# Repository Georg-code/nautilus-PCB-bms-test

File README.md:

# Generation complete!
# NAUTILUS Bms Test Board

# Include documentation here
The documentation can be very similar to your wiki article

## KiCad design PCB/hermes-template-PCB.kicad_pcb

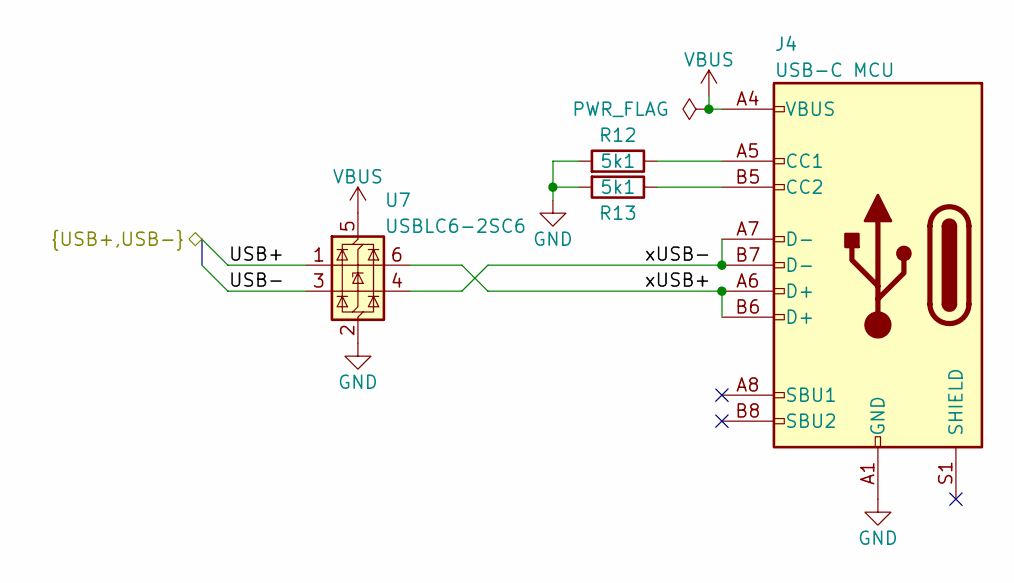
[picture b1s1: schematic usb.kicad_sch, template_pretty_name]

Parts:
J4: USB-C MCU; USB_C_Receptacle_GCT_USB4105-xx-A_16P_TopMnt_Horizontal; Part No. 629722000214
R12, R13: 5k1; R_0603_1608Metric; Part No. CRCW06035K10FKEAC
U7: USBLC6-2SC6; SOT-23-6; Part No. 82400102

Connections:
/Microcontroller/USB+: U7.1 (I/O1); also elsewhere on the board
/Microcontroller/USB-: U7.3 (I/O2); also elsewhere on the board
/USB Connector/xUSB+: J4.A6 (D+), J4.B6 (D+), U7.6 (I/O1)
/USB Connector/xUSB-: J4.A7 (D-), J4.B7 (D-), U7.4 (I/O2)
GND: J4.A1 (GND), J4.A12 (GND), J4.B1 (GND), J4.B12 (GND), R12.1, R13.1, U7.2 (GND); also elsewhere on the board
unnamed: J4.A5 (CC1), R12.2
unnamed: J4.B5 (CC2), R13.2
VBUS: J4.A4 (VBUS), J4.A9 (VBUS), J4.B4 (VBUS), J4.B9 (VBUS), U7.5 (VBUS); also elsewhere on the board

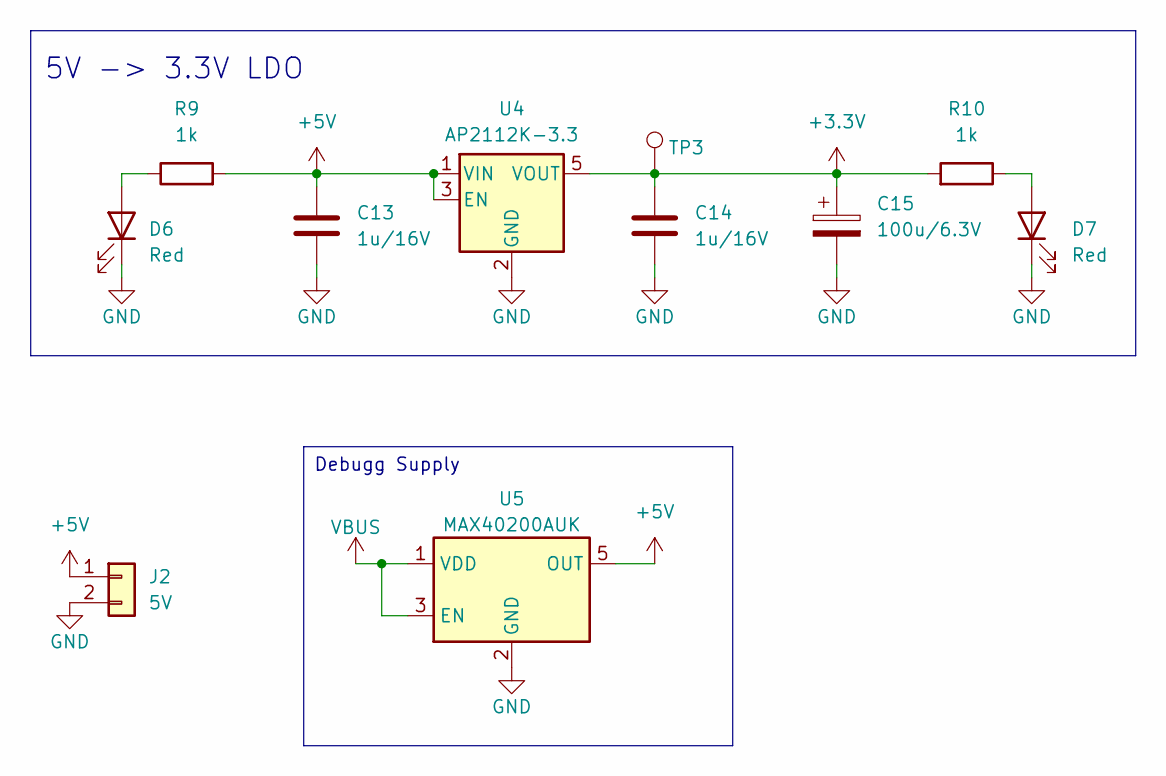
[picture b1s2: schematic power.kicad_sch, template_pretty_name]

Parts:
C13, C14: 1u/16V; C_0603_1608Metric; Part No. 885012206052
C15: 100u/6.3V; CP_EIA-7343-20_Kemet-V; Part No. 875015119003
D6, D7: Red; LED_0603_1608Metric; Part No. 150060RS75000
J2: 5V; PinHeader_2x01_P2.54mm_Vertical; Part No. 61300211121
R9, R10: 1k; R_0603_1608Metric; Part No. CRCW06031K00FKEAC
TP3: TestPoint; TestPoint_THTPad_D2.0mm_Drill1.0mm
U4: AP2112K-3.3; SOT-23-5; Part No. AP2112K-3.3TRG1
U5: MAX40200AUK; SOT-23-5; Part No. MAX40200AUK

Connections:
+3.3V: C14.1, C15.1, R10.1, TP3.1, U4.5 (VOUT); also elsewhere on the board
+5V: C13.1, J2.1, R9.1, U4.1 (VIN), U4.3 (EN), U5.5 (OUT); also elsewhere on the board
GND: C13.2, C14.2, C15.2, D6.1 (K), D7.1 (K), J2.2, U4.2 (GND), U5.2 (GND); also elsewhere on the board
unnamed: D6.2 (A), R9.2
unnamed: D7.2 (A), R10.2
VBUS: U5.1 (VDD), U5.3 (EN); also elsewhere on the board

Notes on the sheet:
5V -> 3.3V LDO
Debugg Supply

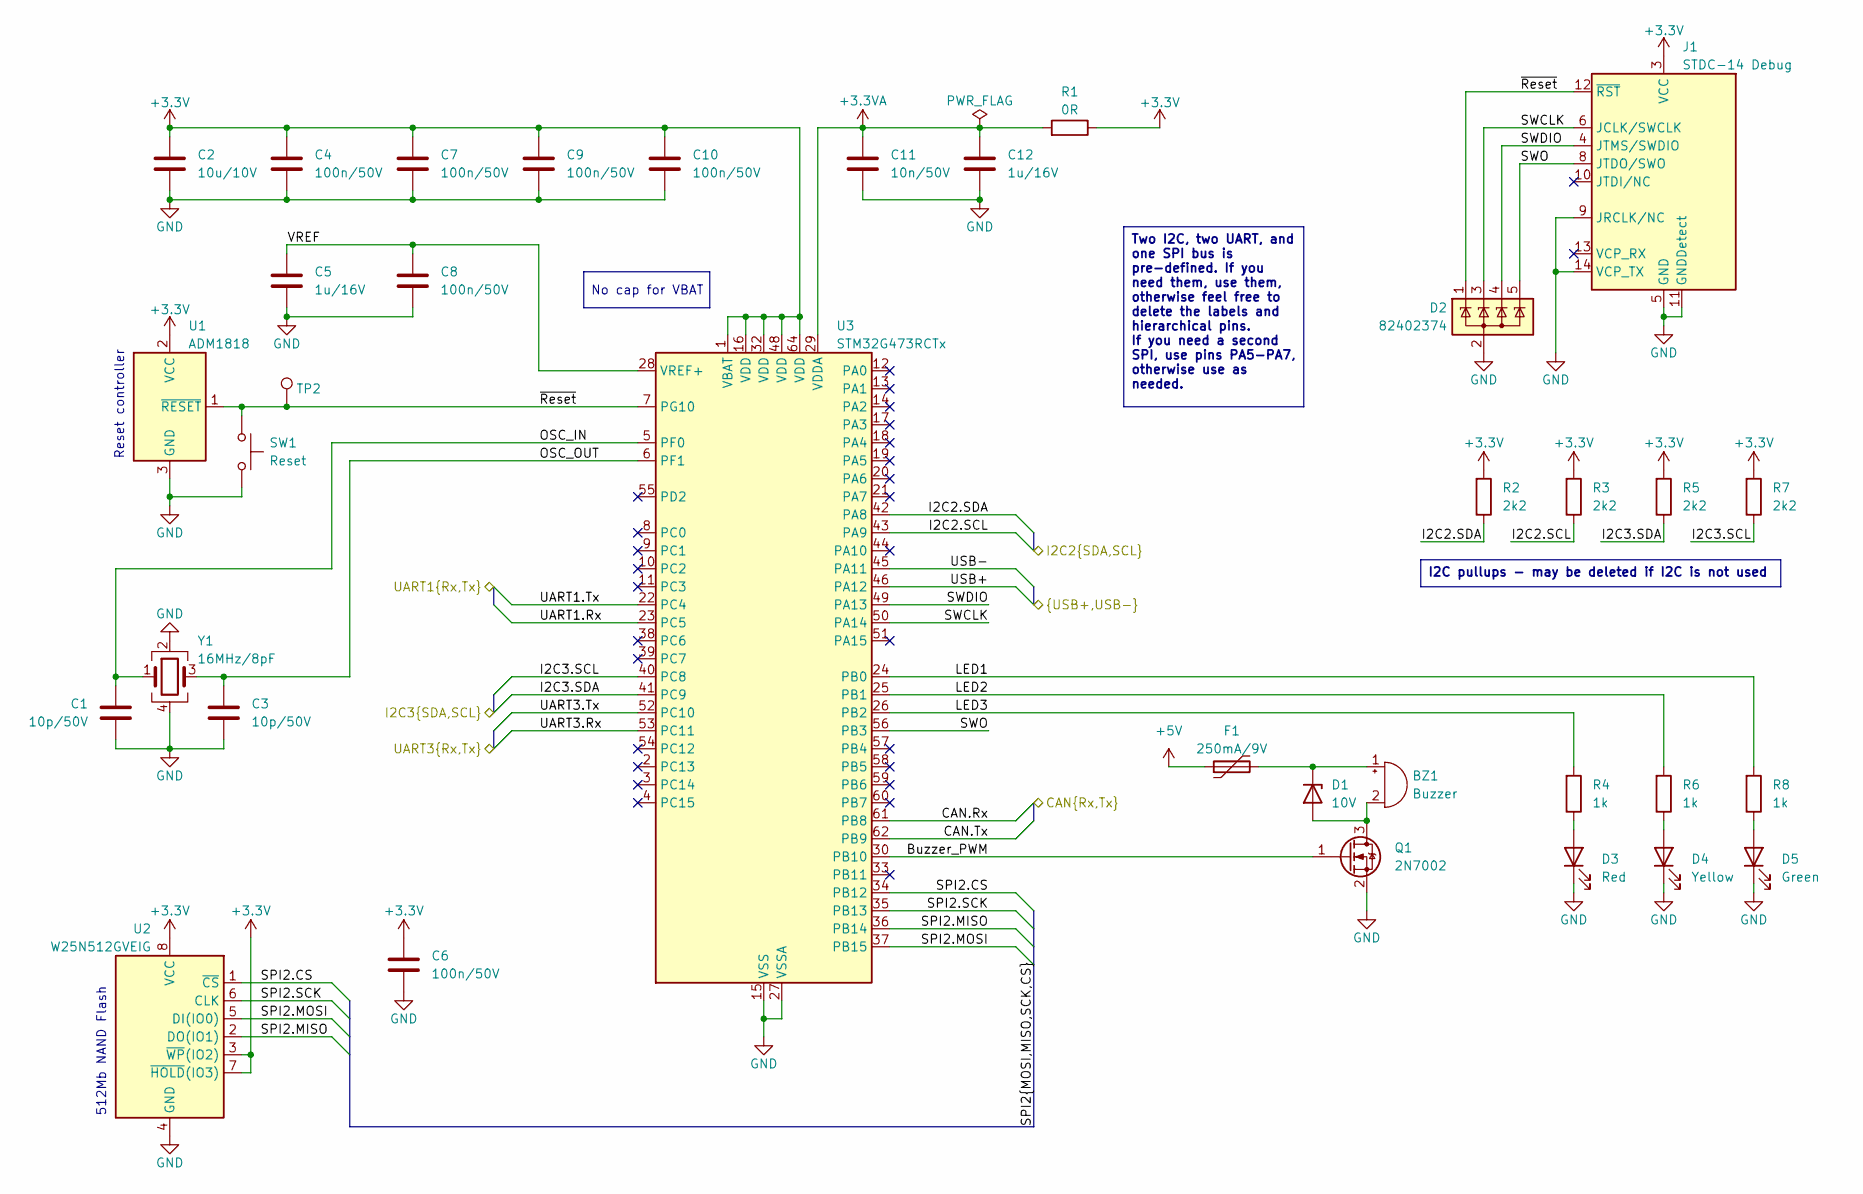
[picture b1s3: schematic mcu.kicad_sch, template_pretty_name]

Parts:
BZ1: Buzzer; Buzzer_CUI_CMT-8504-100-SMT-TR; Part No. CMT-8504-100-SMT-TR
C1, C3: 10p/50V; C_0603_1608Metric; Part No. 885012006051
C2: 10u/10V; C_0805_2012Metric; Part No. 885012207026
C4, C6, C7, C8, C9, C10: 100n/50V; C_0603_1608Metric; Part No. 885012206095
C5, C12: 1u/16V; C_0603_1608Metric; Part No. 885012206052
C11: 10n/50V; C_0603_1608Metric; Part No. 885012206089
D1: 10V; D_SOD-523; Part No. BZT52C10T-7
D2: 82402374; SOT-353_SC-70-5; Part No. 82402374
D3: Red; LED_0603_1608Metric; Part No. 150060RS75000
D4: Yellow; LED_0603_1608Metric; Part No. 150060YS75000
D5: Green; LED_0603_1608Metric; Part No. 150060GS75000
F1: 250mA/9V; Fuse_0603_1608Metric; Part No. 0603L025YR
J1: STDC-14 Debug; IDC-Header_2x07_P1.27mm_Vertical_SMD; Part No. 62701420621
Q1: 2N7002; SOT-23; Part No. 2N7002NXBKR
R1: 0R; R_0603_1608Metric; Part No. CRCW06030000Z0EAC
R2, R3, R5, R7: 2k2; R_0603_1608Metric; Part No. CRCW06032K20FKEAC
R4, R6, R8: 1k; R_0603_1608Metric; Part No. CRCW06031K00FKEAC
SW1: Reset; SW_Push_Wuerth_434123025826; Part No. 434123025826
TP2: TestPoint; TestPoint_THTPad_D2.0mm_Drill1.0mm
U1: ADM1818; SOT-23; Part No. ADM1818-20ARTZ-RL7
U2: W25N512GVEIG; WSON-8-1EP_8x6mm_P1.27mm_EP3.4x4.3mm; Part No. W25N512GVEIG
U3: STM32G473RCTx; LQFP-64_10x10mm_P0.5mm; Part No. STM32G473RCT6
Y1: 16MHz/8pF; Crystal_SMD_3225-4Pin_3.2x2.5mm; Part No. 830064296

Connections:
+3.3V: C2.1, C4.1, C6.1, C7.1, C9.1, C10.1, J1.3 (VCC), R1.2, R2.1, R3.1, R5.1, R7.1, U1.2 (VCC), U2.3 (~WP(IO2)), U2.7 (~HOLD(IO3)), U2.8 (VCC), U3.1 (VBAT), U3.16 (VDD), U3.32 (VDD), U3.48 (VDD), U3.64 (VDD); also elsewhere on the board
+3.3VA: C11.1, C12.1, R1.1, U3.29 (VDDA)
+5V: F1.1; also elsewhere on the board
/CAN Transceiver/CAN.Rx: U3.61 (PB8); also elsewhere on the board
/CAN Transceiver/CAN.Tx: U3.62 (PB9); also elsewhere on the board
/Microcontroller/Buzzer_PWM: Q1.1 (G), U3.30 (PB10)
/Microcontroller/I2C2.SCL: R3.2, U3.43 (PA9)
/Microcontroller/I2C2.SDA: R2.2, U3.42 (PA8)
/Microcontroller/I2C3.SCL: R7.2, U3.40 (PC8)
/Microcontroller/I2C3.SDA: R5.2, U3.41 (PC9)
/Microcontroller/LED1: R8.1, U3.24 (PB0)
/Microcontroller/LED2: R6.1, U3.25 (PB1)
/Microcontroller/LED3: R4.1, U3.26 (PB2)
/Microcontroller/OSC_IN: C1.1, U3.5 (PF0), Y1.1
/Microcontroller/OSC_OUT: C3.1, U3.6 (PF1), Y1.3
/Microcontroller/SPI2.CS: U2.1 (~CS), U3.34 (PB12)
/Microcontroller/SPI2.MISO: U2.2 (DO(IO1)), U3.36 (PB14)
/Microcontroller/SPI2.MOSI: U2.5 (DI(IO0)), U3.37 (PB15)
/Microcontroller/SPI2.SCK: U2.6 (CLK), U3.35 (PB13)
/Microcontroller/SWCLK: D2.3 (K), J1.6 (JCLK/SWCLK), U3.50 (PA14)
/Microcontroller/SWDIO: D2.4 (K), J1.4 (JTMS/SWDIO), U3.49 (PA13)
/Microcontroller/SWO: D2.5 (K), J1.8 (JTDO/SWO), U3.56 (PB3)
/Microcontroller/UART1.Rx: U3.23 (PC5)
/Microcontroller/UART1.Tx: U3.22 (PC4)
/Microcontroller/UART3.Rx: U3.53 (PC11)
/Microcontroller/UART3.Tx: U3.52 (PC10)
/Microcontroller/USB+: U3.46 (PA12); also elsewhere on the board
/Microcontroller/USB-: U3.45 (PA11); also elsewhere on the board
/Microcontroller/VREF: C5.1, C8.1, U3.28 (VREF+)
/Microcontroller/~Reset: D2.1 (K), J1.12 (~RST), SW1.1, TP2.1, U1.1 (~RESET), U3.7 (PG10)
GND: C1.2, C2.2, C3.2, C4.2, C5.2, C6.2, C7.2, C8.2, C9.2, C10.2, C11.2, C12.2, D2.2 (A), D3.1 (K), D4.1 (K), D5.1 (K), J1.5 (GND), J1.7 (GND), J1.9 (JRCLK/NC), J1.11 (GNDDetect), J1.14 (VCP_TX), Q1.2 (S), SW1.2, U1.3 (GND), U2.4 (GND), U3.15 (VSS), U3.27 (VSSA), U3.31 (VSS), U3.47 (VSS), U3.63 (VSS), Y1.2, Y1.4; also elsewhere on the board
unnamed: BZ1.1 (+), D1.1 (K), F1.2
unnamed: BZ1.2 (-), D1.2 (A), Q1.3 (D)
unnamed: D3.2 (A), R4.2
unnamed: D4.2 (A), R6.2
unnamed: D5.2 (A), R8.2

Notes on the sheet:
512Mb NAND Flash
Reset controller
Two I2C, two UART, and one SPI bus is pre-defined. If you need them, use them, otherwise feel free to delete the labels and hierarchical pins. If you need a second SPI, use pins PA5-PA7, otherwise use as needed.
I2C pullups - may be deleted if I2C is not used
No cap for VBAT

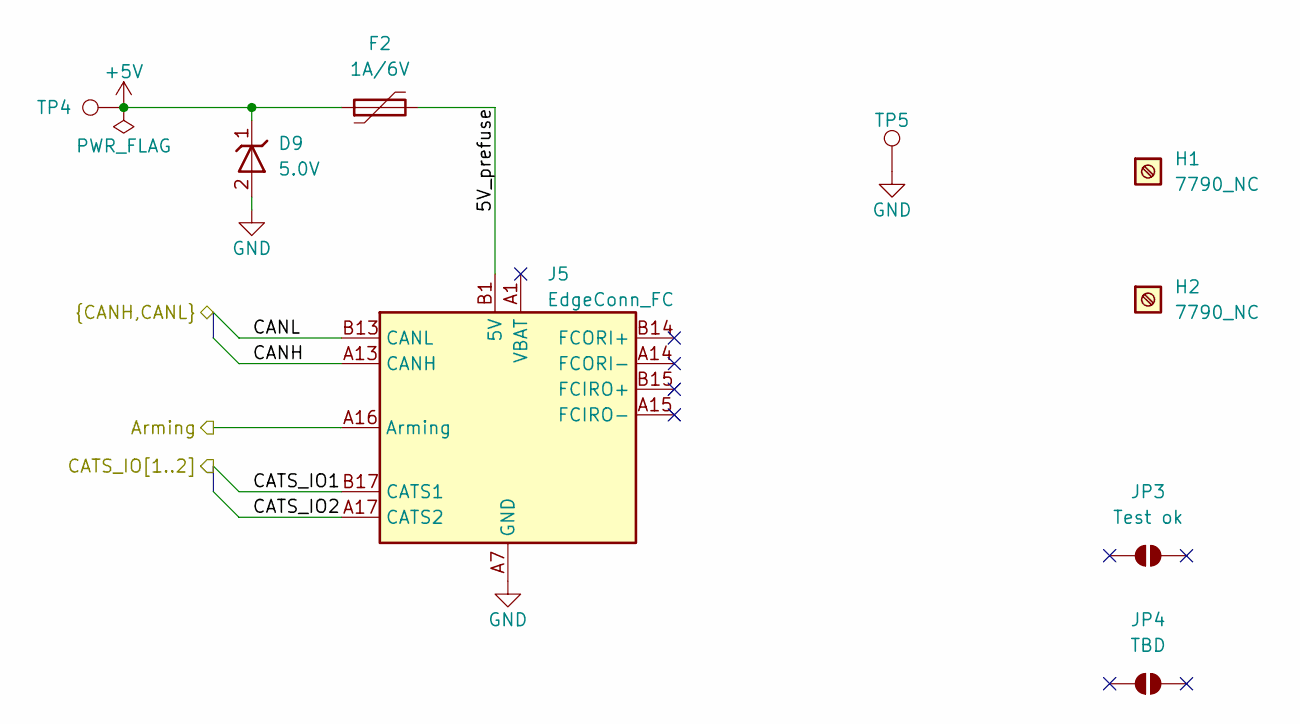
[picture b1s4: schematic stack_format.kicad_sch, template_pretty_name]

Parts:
D9: 5.0V; D_SMA; Part No. 824500500
F2: 1A/6V; Fuse_1206_3216Metric; Part No. NANOSMDC110F-2
H1, H2: 7790_NC; Mounting_Keystone_7790_NC; Part No. 7790
J5: EdgeConn_FC; BUS_PCIexpress_x1; Part No. N/A
JP3: Test ok; SolderJumper-2_P1.3mm_Open_RoundedPad1.0x1.5mm
JP4: TBD; SolderJumper-2_P1.3mm_Open_RoundedPad1.0x1.5mm
TP4: TestPoint; TestPoint_THTPad_D2.0mm_Drill1.0mm
TP5: TestPoint; TestPoint_THTPad_2.0x2.0mm_Drill1.0mm

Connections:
+5V: D9.1 (K), F2.1, TP4.1; also elsewhere on the board
/Backplane connector, mounting/5V_prefuse: F2.2, J5.B1 (5V), J5.B2 (5V), J5.B3 (5V), J5.B4 (5V), J5.B5 (5V), J5.B6 (5V)
/Backplane connector, mounting/Arming: J5.A16 (Arming)
/Backplane connector, mounting/CANH: J5.A13 (CANH); also elsewhere on the board
/Backplane connector, mounting/CANL: J5.B13 (CANL); also elsewhere on the board
/Backplane connector, mounting/CATS_IO1: J5.B17 (CATS1)
/Backplane connector, mounting/CATS_IO2: J5.A17 (CATS2)
GND: D9.2 (A), J5.A7 (GND), J5.A8 (GND), J5.A9 (GND), J5.A10 (GND), J5.A11 (GND), J5.A12 (GND), J5.B7 (GND), J5.B8 (GND), J5.B9 (GND), J5.B10 (GND), J5.B11 (GND), J5.B12 (GND), TP5.1; also elsewhere on the board

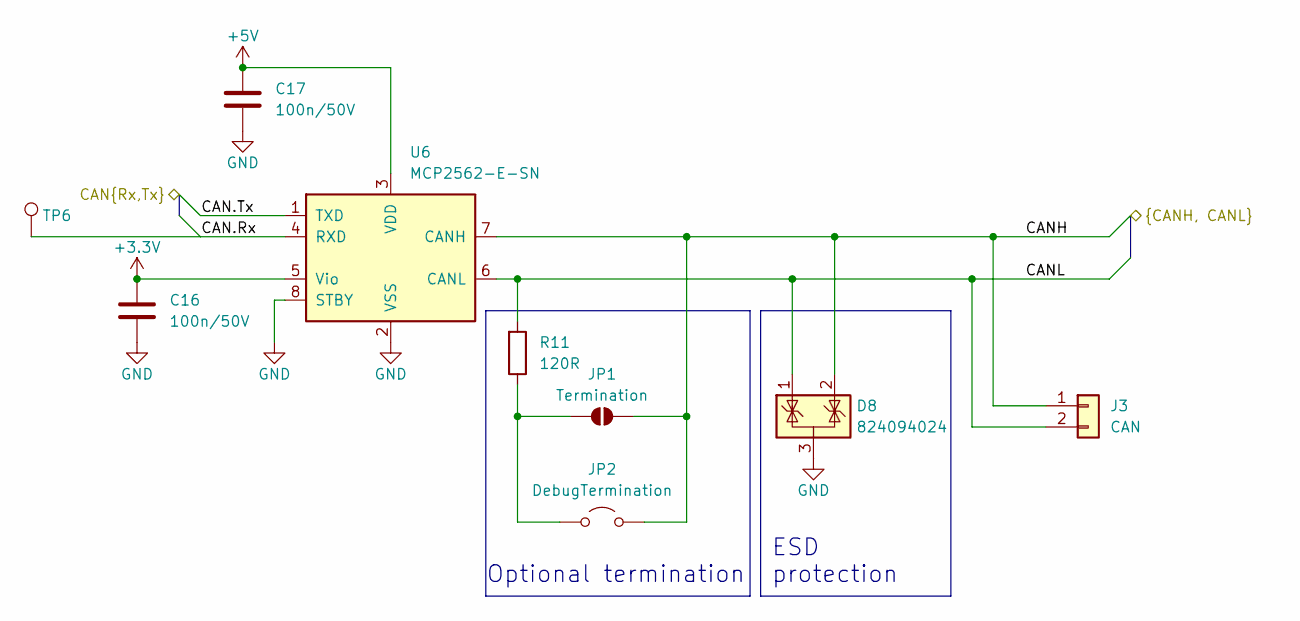
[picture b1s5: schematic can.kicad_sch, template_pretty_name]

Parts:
C16, C17: 100n/50V; C_0603_1608Metric; Part No. 885012206095
D8: 824094024; SOT-23; Part No. 824094024
J3: CAN; PinHeader_2x01_P2.54mm_Vertical; Part No. 61300211121
JP1: Termination; SolderJumper-2_P1.3mm_Open_TrianglePad1.0x1.5mm
JP2: DebugTermination; PinHeader_1x02_P2.54mm_Vertical; Part No. 61300211121
R11: 120R; R_0603_1608Metric; Part No. CRCW0603120RFKEAC
TP6: TestPoint; TestPoint_THTPad_D2.0mm_Drill1.0mm
U6: MCP2562-E-SN; SOIC-8_3.9x4.9mm_P1.27mm; Part No. MCP2562FD-x-SN

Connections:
+3.3V: C16.1, U6.5 (Vio); also elsewhere on the board
+5V: C17.1, U6.3 (VDD); also elsewhere on the board
/Backplane connector, mounting/CANH: D8.2 (K), J3.1, JP1.2 (B), JP2.2 (B), U6.7 (CANH); also elsewhere on the board
/Backplane connector, mounting/CANL: D8.1 (K), J3.2, R11.1, U6.6 (CANL); also elsewhere on the board
/CAN Transceiver/CAN.Rx: TP6.1, U6.4 (RXD); also elsewhere on the board
/CAN Transceiver/CAN.Tx: U6.1 (TXD); also elsewhere on the board
GND: C16.2, C17.2, D8.3 (A), U6.2 (VSS), U6.8 (STBY); also elsewhere on the board
unnamed: JP1.1 (A), JP2.1 (A), R11.2

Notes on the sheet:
ESD protection
Optional termination

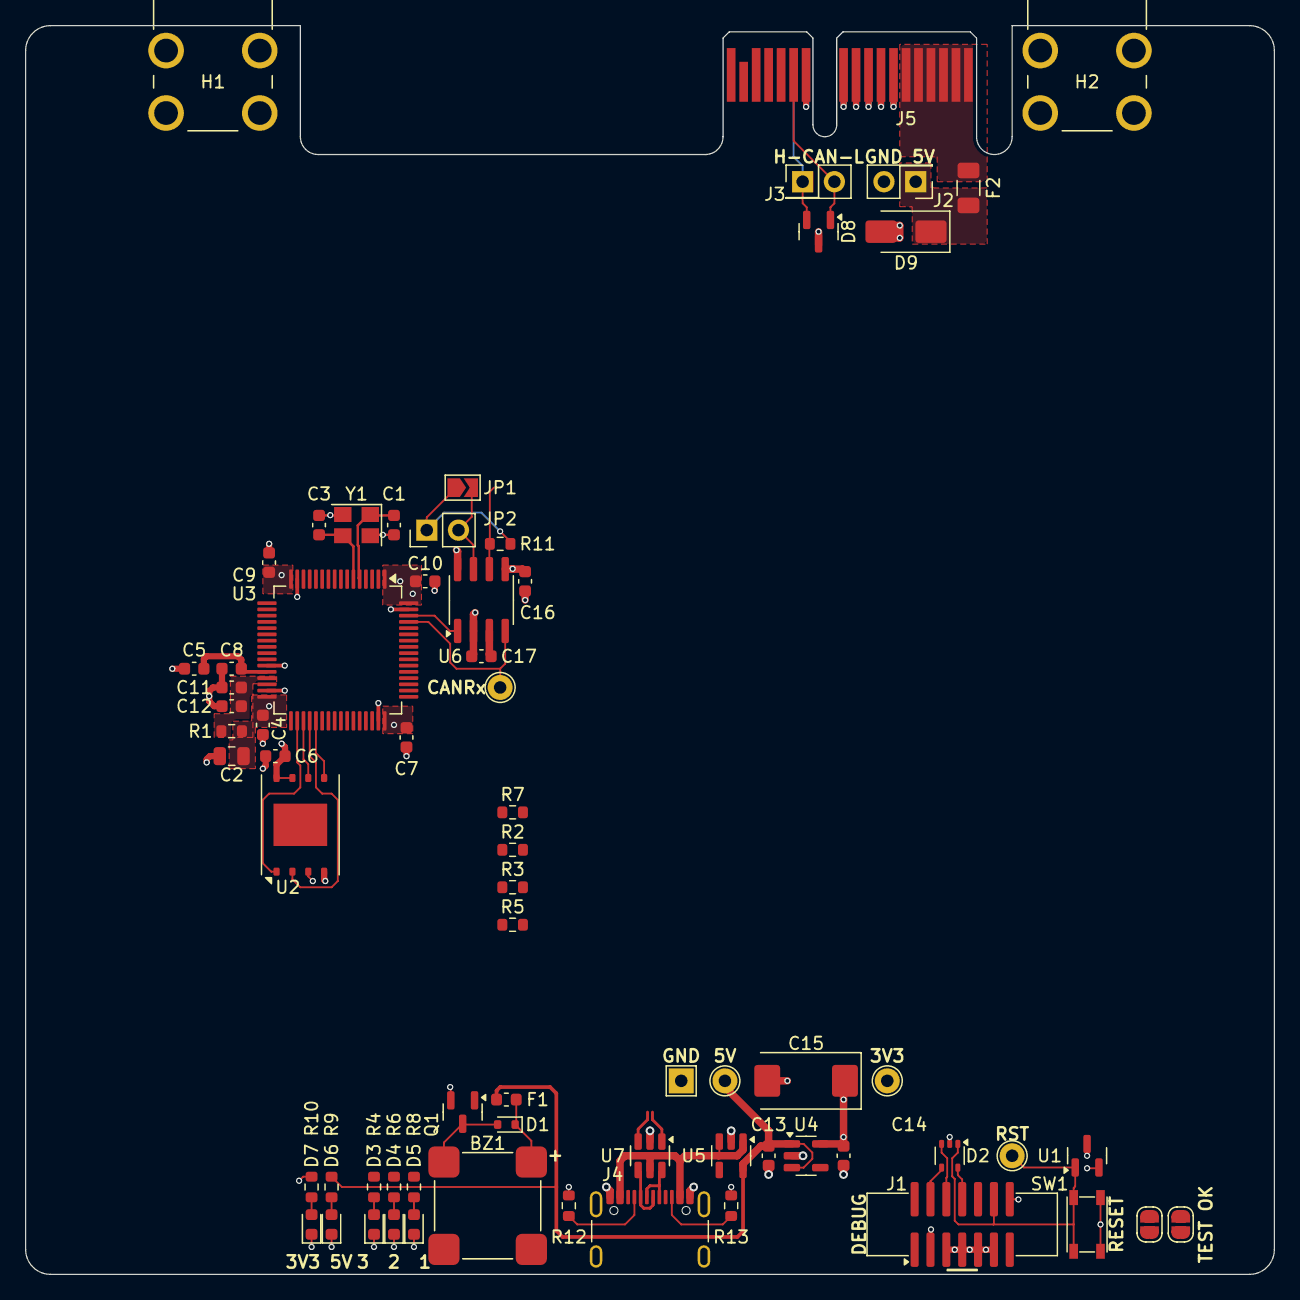
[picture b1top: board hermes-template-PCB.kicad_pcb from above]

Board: 4 copper layers, 100.0 x 100.0 mm, 68 parts (0 on the bottom side), 43 nets.

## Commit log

2025-12-09 Generate project from template
